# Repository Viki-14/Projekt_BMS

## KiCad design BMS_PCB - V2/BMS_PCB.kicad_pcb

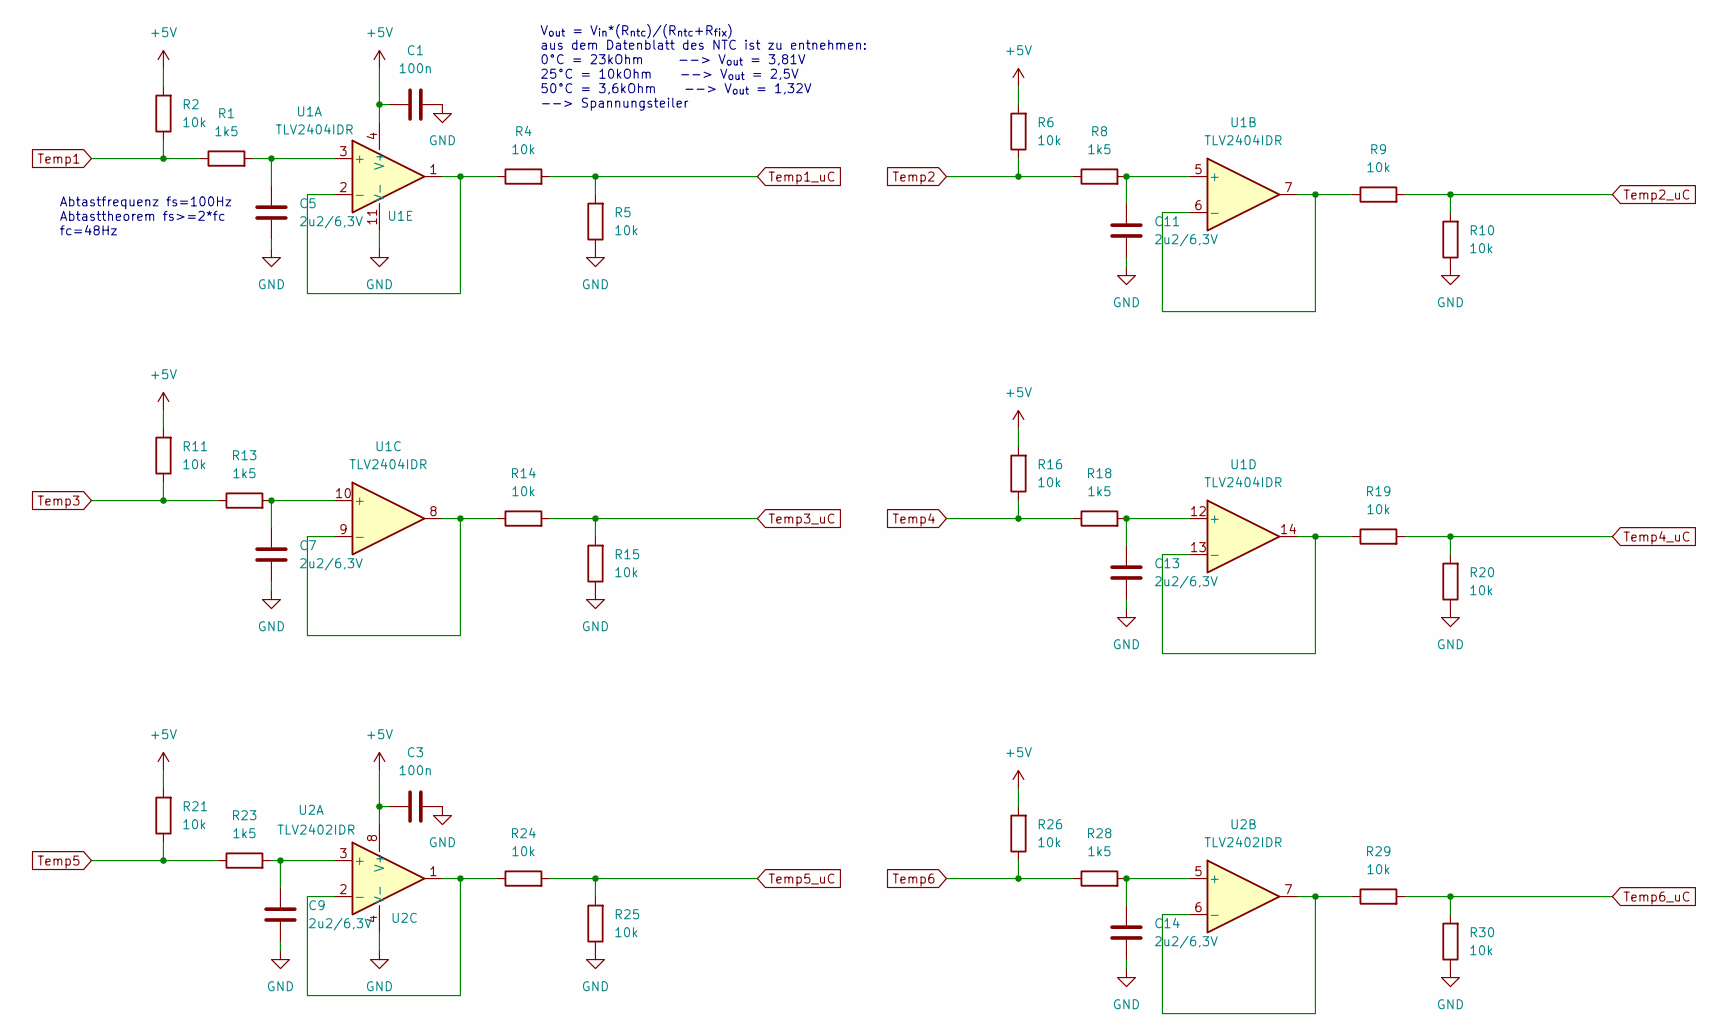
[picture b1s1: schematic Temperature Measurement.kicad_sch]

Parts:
C1, C3: 100n; C_0603_1608Metric_Pad1.08x0.95mm_HandSolder
C5, C7, C9, C11, C13, C14: 2u2/6,3V; C_0603_1608Metric_Pad1.08x0.95mm_HandSolder
R1, R8, R13, R18, R23, R28: 1k5; R_0603_1608Metric_Pad0.98x0.95mm_HandSolder
R2, R4, R5, R6, R9, R10, R11, R14, R15, R16, R19, R20, R21, R24, R25, R26, R29, R30: 10k; R_0603_1608Metric_Pad0.98x0.95mm_HandSolder
U1: TLV2404IDR; SOIC-14_3.9x8.7mm_P1.27mm
U2: TLV2402IDR; SOIC-8_3.9x4.9mm_P1.27mm

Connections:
+5V: C1.1, C3.1, R2.2, R6.2, R11.2, R16.2, R21.2, R26.2, U1.4 (V+), U2.8 (V+); also elsewhere on the board
GND: C1.2, C3.2, C5.2, C7.2, C9.2, C11.2, C13.2, C14.2, R5.1, R10.1, R15.1, R20.1, R25.1, R30.1, U1.11 (V-), U2.4 (V-); also elsewhere on the board
unnamed: C5.1, R1.2, U1.3 (+)
unnamed: R4.1, U1.1, U1.2 (-)
unnamed: C11.1, R8.2, U1.5 (+)
unnamed: R9.1, U1.6 (-), U1.7
unnamed: C7.1, R13.2, U1.10 (+)
unnamed: R14.1, U1.8, U1.9 (-)
unnamed: C13.1, R18.2, U1.12 (+)
unnamed: R19.1, U1.13 (-), U1.14
unnamed: C9.1, R23.2, U2.3 (+)
unnamed: R24.1, U2.1, U2.2 (-)
unnamed: C14.1, R28.2, U2.5 (+)
unnamed: R29.1, U2.6 (-), U2.7
Temp1: R1.1, R2.1; also elsewhere on the board
Temp1_uC: R4.2, R5.2; also elsewhere on the board
Temp2: R6.1, R8.1; also elsewhere on the board
Temp2_uC: R9.2, R10.2; also elsewhere on the board
Temp3: R11.1, R13.1; also elsewhere on the board
Temp3_uC: R14.2, R15.2; also elsewhere on the board
Temp4: R16.1, R18.1; also elsewhere on the board
Temp4_uC: R19.2, R20.2; also elsewhere on the board
Temp5: R21.1, R23.1; also elsewhere on the board
Temp5_uC: R24.2, R25.2; also elsewhere on the board
Temp6: R26.1, R28.1; also elsewhere on the board
Temp6_uC: R29.2, R30.2; also elsewhere on the board

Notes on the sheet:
V_{out} = V_{in}*(R_{ntc})/(R_{ntc}+R_{fix}) aus dem Datenblatt des NTC ist zu entnehmen: 0°C = 23kOhm --> V_{out} = 3,81V 25°C = 10kOhm --> V_{out} = 2,5V 50°C = 3,6kOhm --> V_{out} = 1,32V --> Spannungsteiler
Abtastfrequenz fs=100Hz Abtasttheorem fs>=2*fc fc=48Hz

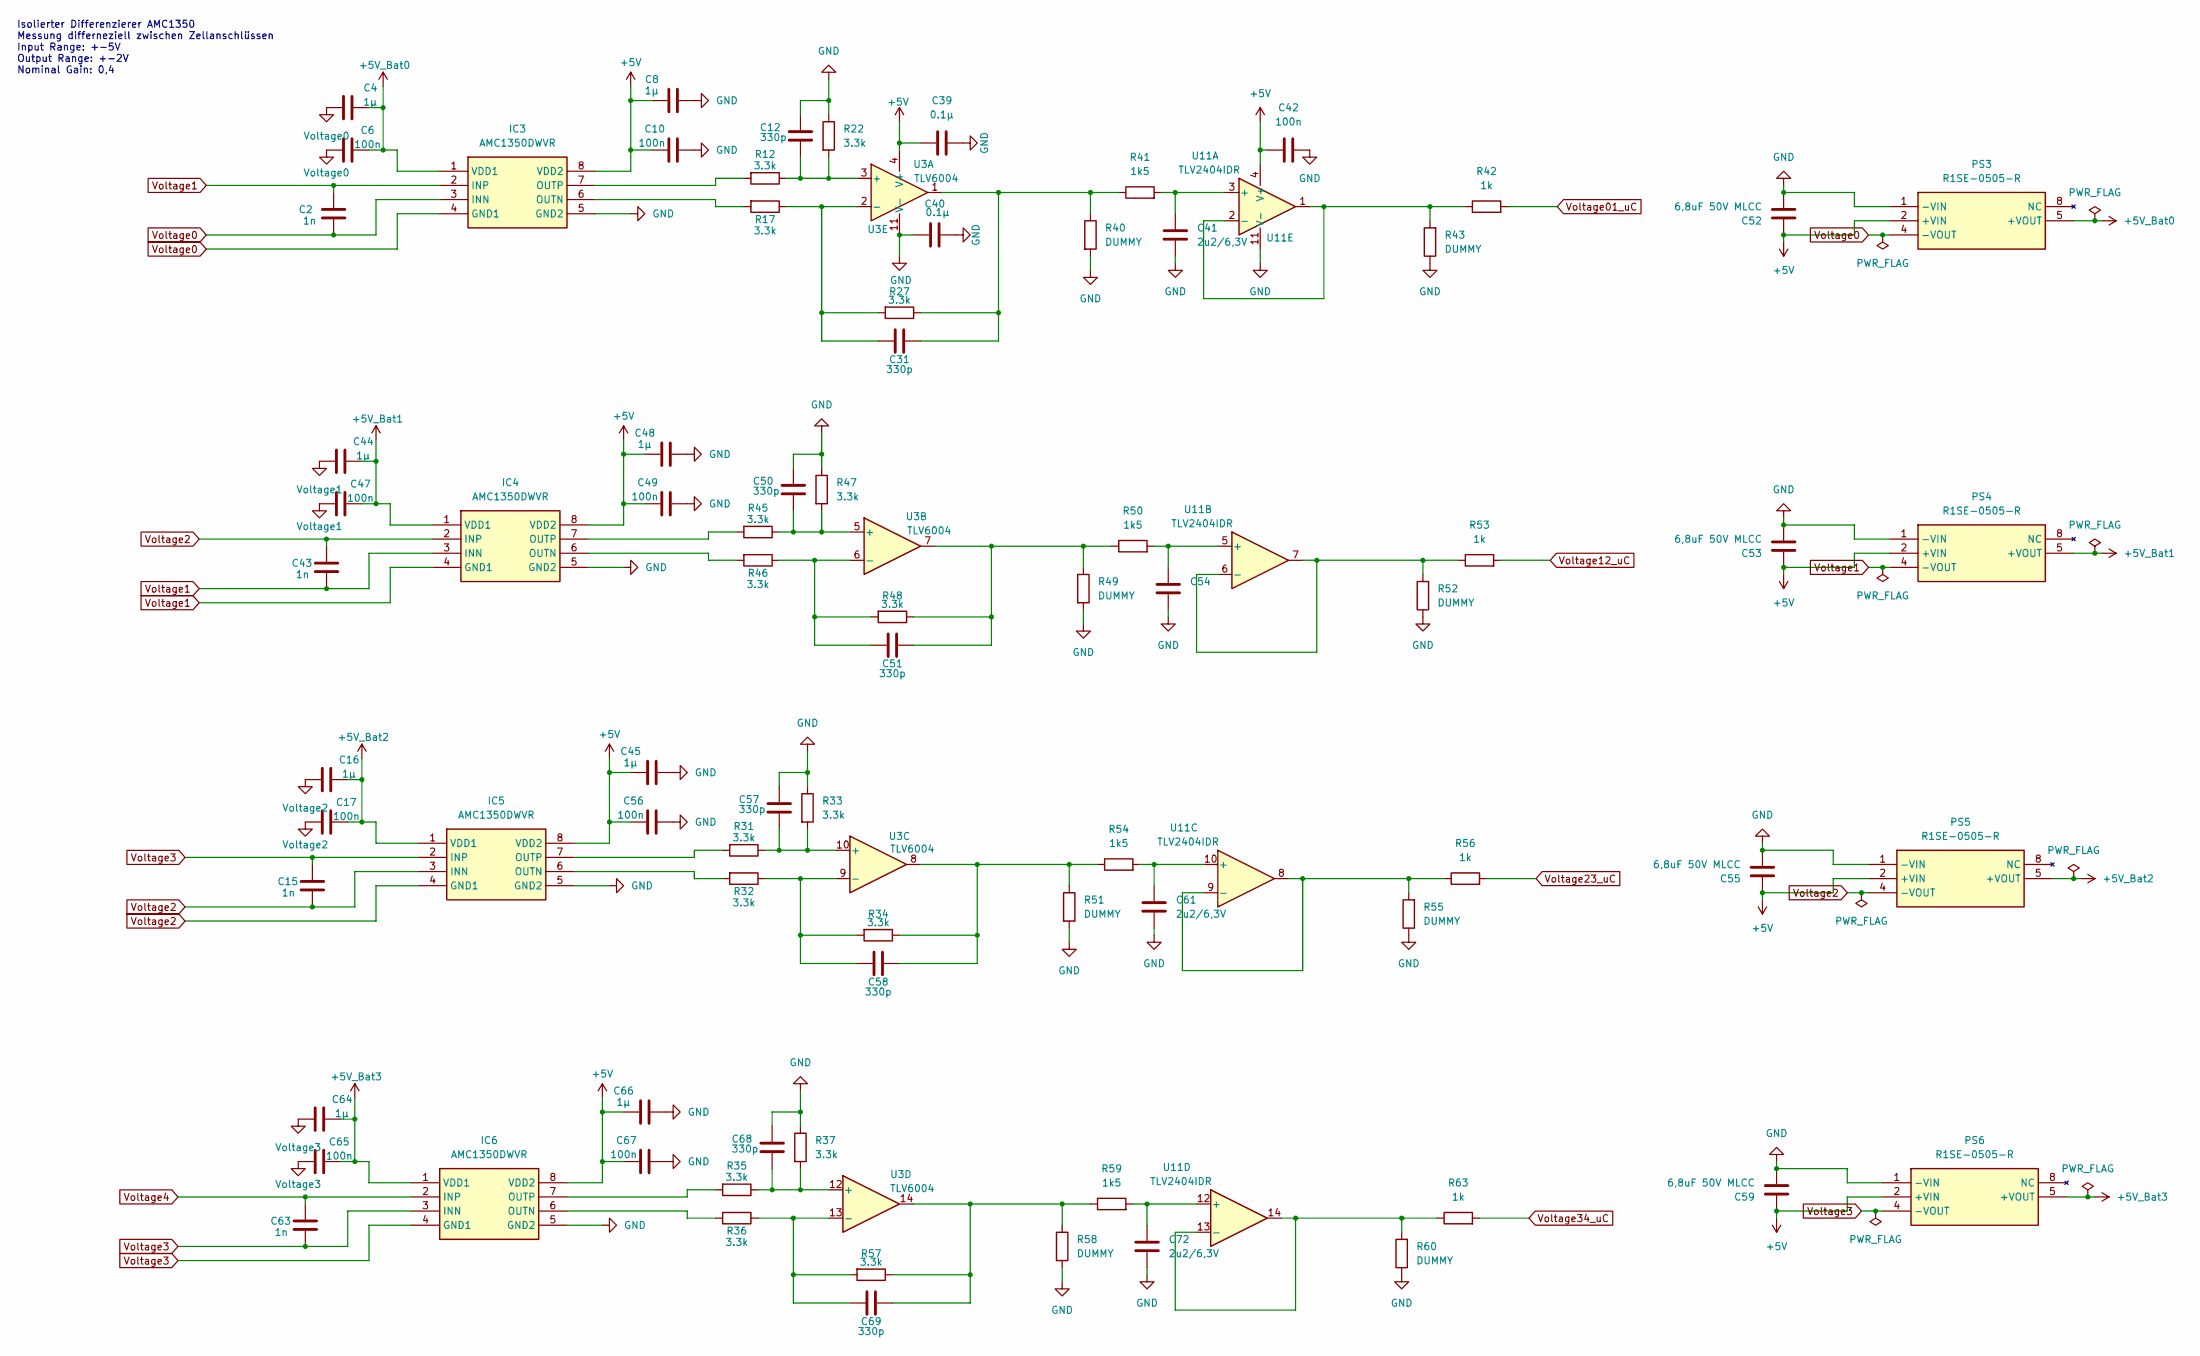
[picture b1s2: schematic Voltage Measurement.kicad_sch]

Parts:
C2, C15, C43, C63: 1n; C_0603_1608Metric_Pad1.08x0.95mm_HandSolder
C4, C8, C16, C44, C45, C48, C64, C66: 1µ; C_0603_1608Metric_Pad1.08x0.95mm_HandSolder
C6, C10, C17, C42, C47, C49, C56, C65, C67: 100n; C_0603_1608Metric_Pad1.08x0.95mm_HandSolder
C12, C31, C50, C51, C57, C58, C68, C69: 330p; C_0603_1608Metric_Pad1.08x0.95mm_HandSolder
C39, C40: 0.1µ; C_0603_1608Metric_Pad1.08x0.95mm_HandSolder
C41, C54, C61, C72: 2u2/6,3V; C_0603_1608Metric_Pad1.08x0.95mm_HandSolder
C52, C53, C55, C59: 6,8uF 50V MLCC; C_1206_3216Metric_Pad1.33x1.80mm_HandSolder
IC3, IC4, IC5, IC6: AMC1350DWVR; SOIC127P1150X280-8N; Mouser Part Number 595-AMC1350DWVR
PS3, PS4, PS5, PS6: R1SE-0505-R; R1SE0505; Mouser Part Number 919-R1SE-0505-R
R12, R17, R22, R27, R31, R32, R33, R34, R35, R36, R37, R45, R46, R47, R48, R57: 3.3k; R_0603_1608Metric_Pad0.98x0.95mm_HandSolder
R40, R43, R49, R51, R52, R55, R58, R60: DUMMY; R_0603_1608Metric_Pad0.98x0.95mm_HandSolder
R41, R50, R54, R59: 1k5; R_0603_1608Metric_Pad0.98x0.95mm_HandSolder
R42, R53, R56, R63: 1k; R_0603_1608Metric_Pad0.98x0.95mm_HandSolder
U3: TLV6004; TSSOP-14_4.4x5mm_P0.65mm
U11: TLV2404IDR; SOIC-14_3.9x8.7mm_P1.27mm

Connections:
+5V: C8.2, C10.1, C39.1, C42.1, C45.2, C48.2, C49.1, C52.1, C53.1, C55.1, C56.1, C59.1, C66.2, C67.1, IC3.8 (VDD2), IC4.8 (VDD2), IC5.8 (VDD2), IC6.8 (VDD2), PS3.2 (+VIN), PS4.2 (+VIN), PS5.2 (+VIN), PS6.2 (+VIN), U3.4 (V+), U11.4 (V+); also elsewhere on the board
+5V_Bat0: C4.1, C6.2, IC3.1 (VDD1), PS3.5 (+VOUT)
+5V_Bat1: C44.1, C47.2, IC4.1 (VDD1), PS4.5 (+VOUT)
+5V_Bat2: C16.1, C17.2, IC5.1 (VDD1), PS5.5 (+VOUT)
+5V_Bat3: C64.1, C65.2, IC6.1 (VDD1), PS6.5 (+VOUT)
GND: C8.1, C10.2, C12.1, C39.2, C40.1, C40.2, C41.2, C42.2, C45.1, C48.1, C49.2, C50.1, C52.2, C53.2, C54.2, C55.2, C56.2, C57.1, C59.2, C61.2, C66.1, C67.2, C68.1, C72.2, IC3.5 (GND2), IC4.5 (GND2), IC5.5 (GND2), IC6.5 (GND2), PS3.1 (-VIN), PS4.1 (-VIN), PS5.1 (-VIN), PS6.1 (-VIN), R22.1, R33.1, R37.1, R40.2, R43.1, R47.1, R49.2, R51.2, R52.1, R55.1, R58.2, R60.1, U3.11 (V-), U11.11 (V-); also elsewhere on the board
unnamed: C31.2, R27.1, R40.1, R41.1, U3.1
unnamed: C51.2, R48.1, R49.1, R50.1, U3.7
unnamed: C58.2, R34.1, R51.1, R54.1, U3.8
unnamed: C69.2, R57.1, R58.1, R59.1, U3.14
unnamed: IC3.6 (OUTN), R17.2
unnamed: IC3.7 (OUTP), R12.2
unnamed: IC4.6 (OUTN), R46.2
unnamed: IC4.7 (OUTP), R45.2
unnamed: IC5.6 (OUTN), R32.2
unnamed: IC5.7 (OUTP), R31.2
unnamed: IC6.6 (OUTN), R36.2
unnamed: IC6.7 (OUTP), R35.2
unnamed: C12.2, R12.1, R22.2, U3.3 (+)
unnamed: C31.1, R17.1, R27.2, U3.2 (-)
unnamed: C50.2, R45.1, R47.2, U3.5 (+)
unnamed: C51.1, R46.1, R48.2, U3.6 (-)
unnamed: C57.2, R31.1, R33.2, U3.10 (+)
unnamed: C58.1, R32.1, R34.2, U3.9 (-)
unnamed: C68.2, R35.1, R37.2, U3.12 (+)
unnamed: C69.1, R36.1, R57.2, U3.13 (-)
unnamed: C41.1, R41.2, U11.3 (+)
unnamed: R42.1, R43.2, U11.1, U11.2 (-)
unnamed: C54.1, R50.2, U11.5 (+)
unnamed: R52.2, R53.1, U11.6 (-), U11.7
unnamed: C61.1, R54.2, U11.10 (+)
unnamed: R55.2, R56.1, U11.8, U11.9 (-)
unnamed: C72.1, R59.2, U11.12 (+)
unnamed: R60.2, R63.1, U11.13 (-), U11.14
Voltage0: C2.2, C4.2, C6.1, IC3.3 (INN), IC3.4 (GND1), PS3.4 (-VOUT); also elsewhere on the board
Voltage1: C2.1, C43.2, C44.2, C47.1, IC3.2 (INP), IC4.3 (INN), IC4.4 (GND1), PS4.4 (-VOUT); also elsewhere on the board
Voltage01_uC: R42.2; also elsewhere on the board
Voltage2: C15.2, C16.2, C17.1, C43.1, IC4.2 (INP), IC5.3 (INN), IC5.4 (GND1), PS5.4 (-VOUT); also elsewhere on the board
Voltage3: C15.1, C63.2, C64.2, C65.1, IC5.2 (INP), IC6.3 (INN), IC6.4 (GND1), PS6.4 (-VOUT); also elsewhere on the board
Voltage4: C63.1, IC6.2 (INP); also elsewhere on the board
Voltage12_uC: R53.2; also elsewhere on the board
Voltage23_uC: R56.2; also elsewhere on the board
Voltage34_uC: R63.2; also elsewhere on the board

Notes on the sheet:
Isolierter Differenzierer AMC1350 Messung differneziell zwischen Zellanschlüssen Input Range: +-5V Output Range: +-2V Nominal Gain: 0,4

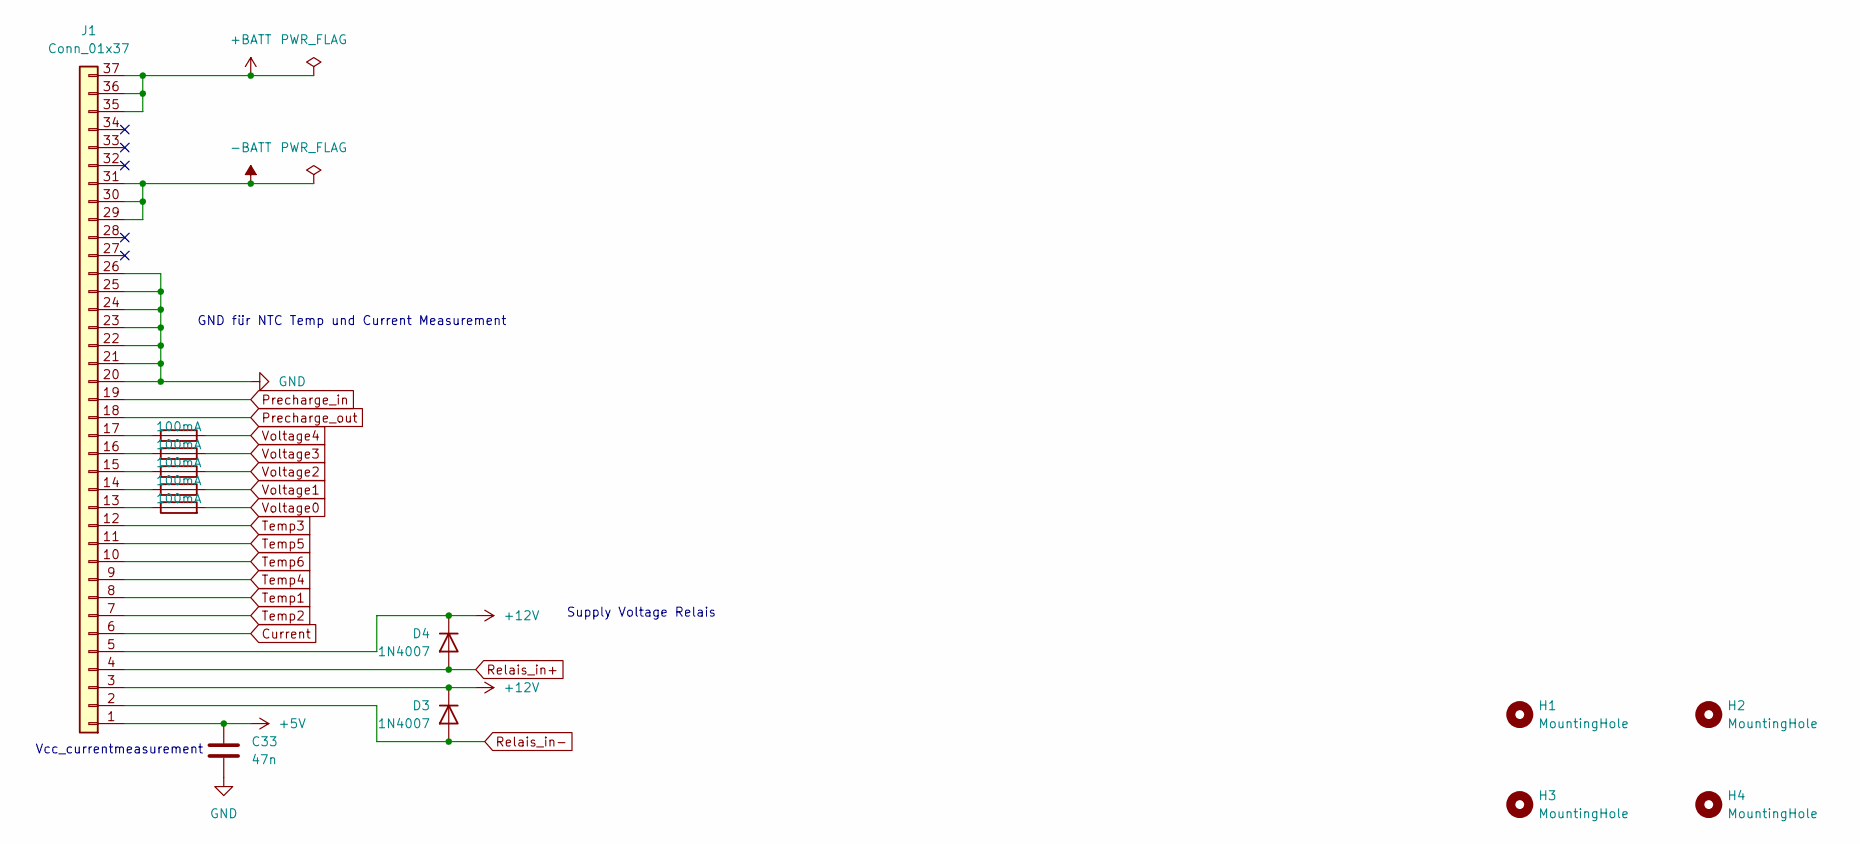
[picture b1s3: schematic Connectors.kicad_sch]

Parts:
C33: 47n; C_0603_1608Metric_Pad1.08x0.95mm_HandSolder
D3, D4: 1N4007; D_SMA
F1, F2, F3, F4, F6: 100mA; Fuse_Littelfuse-NANO2-451_453
H1, H2, H3, H4: MountingHole; MountingHole_3.5mm
J1: Conn_01x37; DSUB-37_Socket_Horizontal_P2.77x2.84mm_EdgePinOffset14.56mm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

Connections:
+12V: D3.1 (K), D4.1 (K), J1.3, J1.5; also elsewhere on the board
+BATT: J1.35, J1.36, J1.37; also elsewhere on the board
-BATT: J1.29, J1.30, J1.31; also elsewhere on the board
Current: J1.6; also elsewhere on the board
GND: C33.2, J1.20, J1.21, J1.22, J1.23, J1.24, J1.25, J1.26; also elsewhere on the board
unnamed: F6.1, J1.13
unnamed: F4.1, J1.14
unnamed: F3.1, J1.15
unnamed: F2.1, J1.16
unnamed: F1.1, J1.17
Precharge_in: J1.19; also elsewhere on the board
Precharge_out: J1.18; also elsewhere on the board
Relais_in+: D4.2 (A), J1.4; also elsewhere on the board
Relais_in-: D3.2 (A), J1.2; also elsewhere on the board
Temp1: J1.8; also elsewhere on the board
Temp2: J1.7; also elsewhere on the board
Temp3: J1.12; also elsewhere on the board
Temp4: J1.9; also elsewhere on the board
Temp5: J1.11; also elsewhere on the board
Temp6: J1.10; also elsewhere on the board
Voltage0: F6.2; also elsewhere on the board
Voltage1: F4.2; also elsewhere on the board
Voltage2: F3.2; also elsewhere on the board
Voltage3: F2.2; also elsewhere on the board
Voltage4: F1.2; also elsewhere on the board

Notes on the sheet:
Supply Voltage Relais
Vcc_currentmeasurement
GND für NTC Temp und Current Measurement

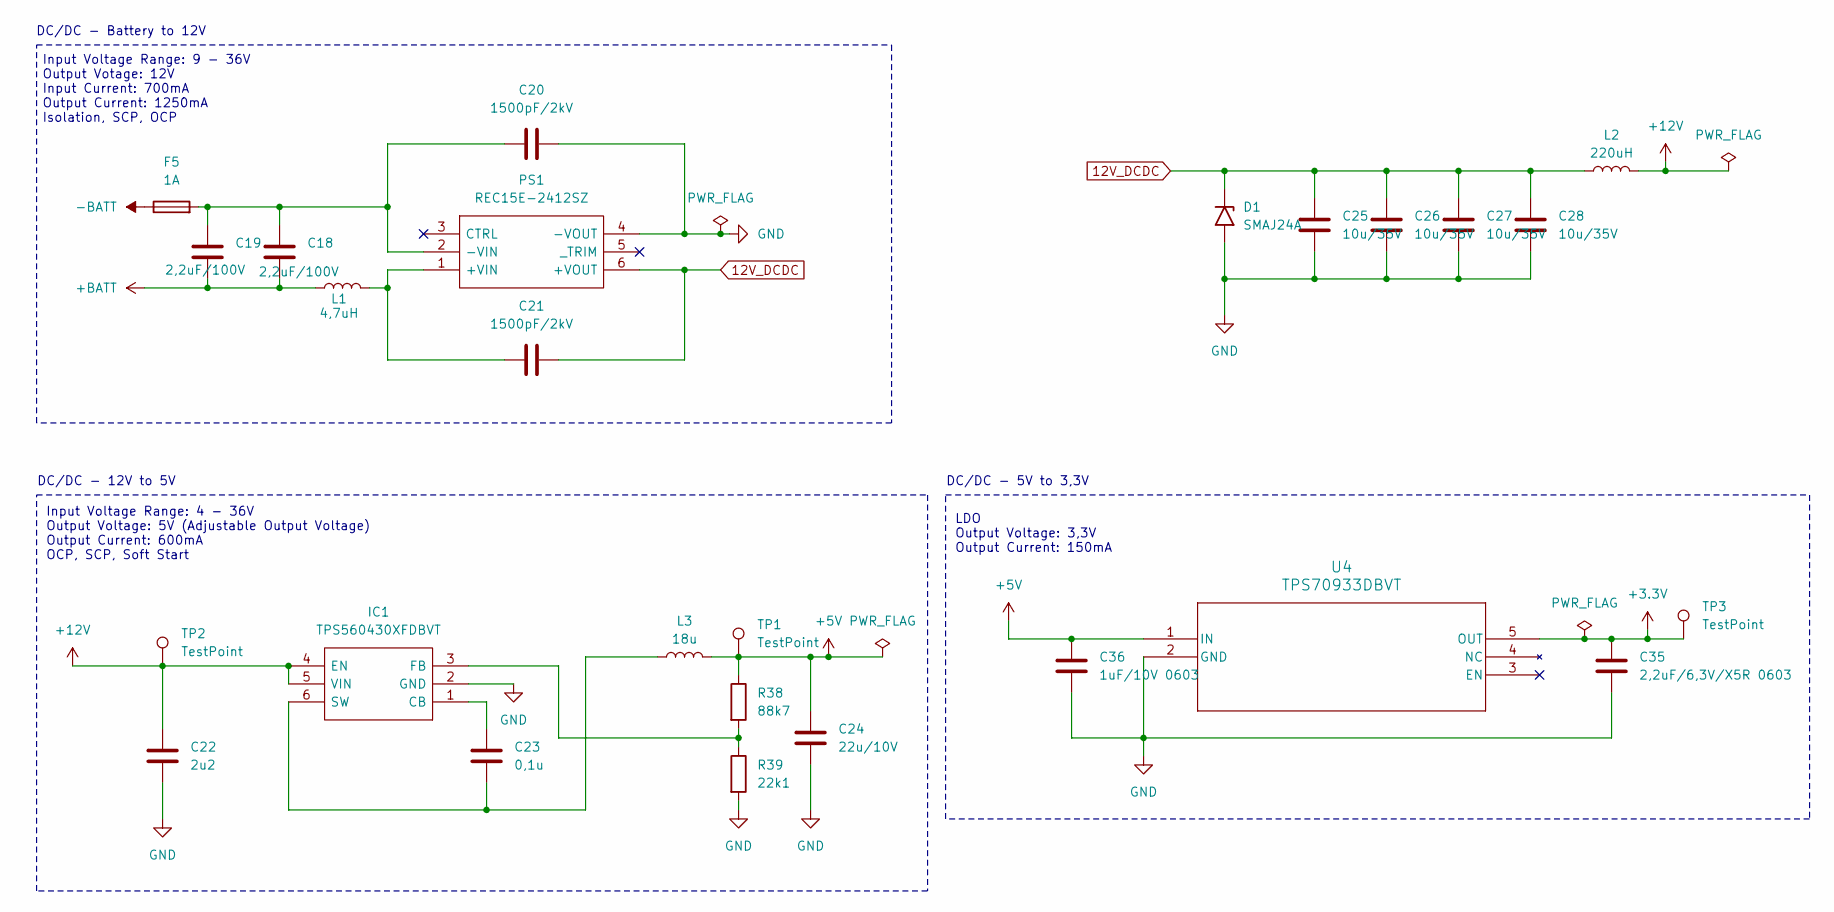
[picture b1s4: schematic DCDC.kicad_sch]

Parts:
C18, C19: 2,2uF/100V; C_0805_2012Metric_Pad1.18x1.45mm_HandSolder
C20, C21: 1500pF/2kV; C_1206_3216Metric_Pad1.33x1.80mm_HandSolder
C22: 2u2; C_0603_1608Metric_Pad1.08x0.95mm_HandSolder
C23: 0,1u; C_0603_1608Metric_Pad1.08x0.95mm_HandSolder
C24: 22u/10V; C_0603_1608Metric_Pad1.08x0.95mm_HandSolder
C25, C26, C27, C28: 10u/35V; C_0603_1608Metric_Pad1.08x0.95mm_HandSolder
C35: 2,2uF/6,3V/X5R 0603; C_0603_1608Metric_Pad1.08x0.95mm_HandSolder
C36: 1uF/10V 0603; C_0603_1608Metric_Pad1.08x0.95mm_HandSolder
D1: SMAJ24A; D_SMA
F5: 1A; Fuseholder_Littelfuse_Nano2_154x
IC1: TPS560430XFDBVT; SOT-23-6_Handsoldering; Mouser Part Number 595-TPS560430XFDBVT
L1: 4,7uH; L_Coilcraft_XxL4020
L2: 220uH; L_Wuerth_WE-PD2-Typ-L
L3: 18u; L_Bourns_SDR0604
PS1: REC15E-2412SZ; CONV_REC15E-2412SZ; Mouser Part Number 919-REC15E-2412SZ
R38: 88k7; R_0603_1608Metric_Pad0.98x0.95mm_HandSolder
R39: 22k1; R_0603_1608Metric_Pad0.98x0.95mm_HandSolder
TP1, TP2, TP3: TestPoint; TestPoint_Pad_D1.0mm
U4: TPS70933DBVT; SOT-23-5_HandSoldering

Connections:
12V_DCDC: C21.2, C25.1, C26.1, C27.1, C28.1, D1.1 (A1), L2.1, PS1.6 (+VOUT)
+5V: C24.1, C36.1, L3.2, R38.1, TP1.1, U4.1 (IN); also elsewhere on the board
+12V: C22.1, IC1.4 (EN), IC1.5 (VIN), L2.2, TP2.1; also elsewhere on the board
+BATT: C18.2, C19.2, L1.1; also elsewhere on the board
-BATT: F5.1; also elsewhere on the board
GND: C20.2, C22.2, C24.2, C25.2, C26.2, C27.2, C28.2, C35.2, C36.2, D1.2 (A2), IC1.2 (GND), PS1.4 (-VOUT), R39.2, U4.2 (GND); also elsewhere on the board
unnamed: C23.1, IC1.1 (CB)
unnamed: IC1.3 (FB), R38.2, R39.1
unnamed: C23.2, IC1.6 (SW), L3.1
unnamed: C21.1, L1.2, PS1.1 (+VIN)
unnamed: C18.1, C19.1, C20.1, F5.2, PS1.2 (-VIN)

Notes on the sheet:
Input Voltage Range: 4 - 36V Output Voltage: 5V (Adjustable Output Voltage) Output Current: 600mA OCP, SCP, Soft Start
DC/DC - Battery to 12V
DC/DC - 12V to 5V
LDO Output Voltage: 3,3V Output Current: 150mA
Input Voltage Range: 9 - 36V Output Votage: 12V Input Current: 700mA Output Current: 1250mA Isolation, SCP, OCP
DC/DC - 5V to 3,3V

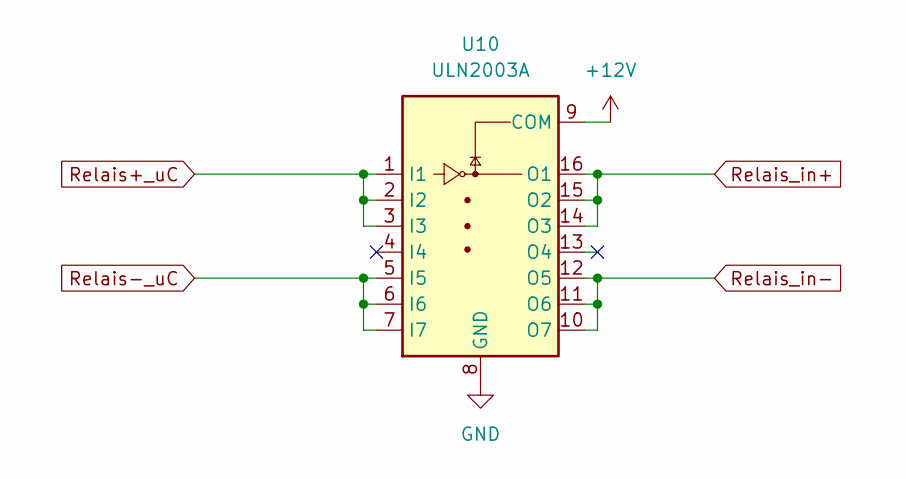
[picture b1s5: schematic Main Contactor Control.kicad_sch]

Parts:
U10: ULN2003A; SOIC-16_3.9x9.9mm_P1.27mm

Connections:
+12V: U10.9 (COM); also elsewhere on the board
GND: U10.8 (GND); also elsewhere on the board
Relais+_uC: U10.1 (I1), U10.2 (I2), U10.3 (I3); also elsewhere on the board
Relais-_uC: U10.5 (I5), U10.6 (I6), U10.7 (I7); also elsewhere on the board
Relais_in+: U10.14 (O3), U10.15 (O2), U10.16 (O1); also elsewhere on the board
Relais_in-: U10.10 (O7), U10.11 (O6), U10.12 (O5); also elsewhere on the board

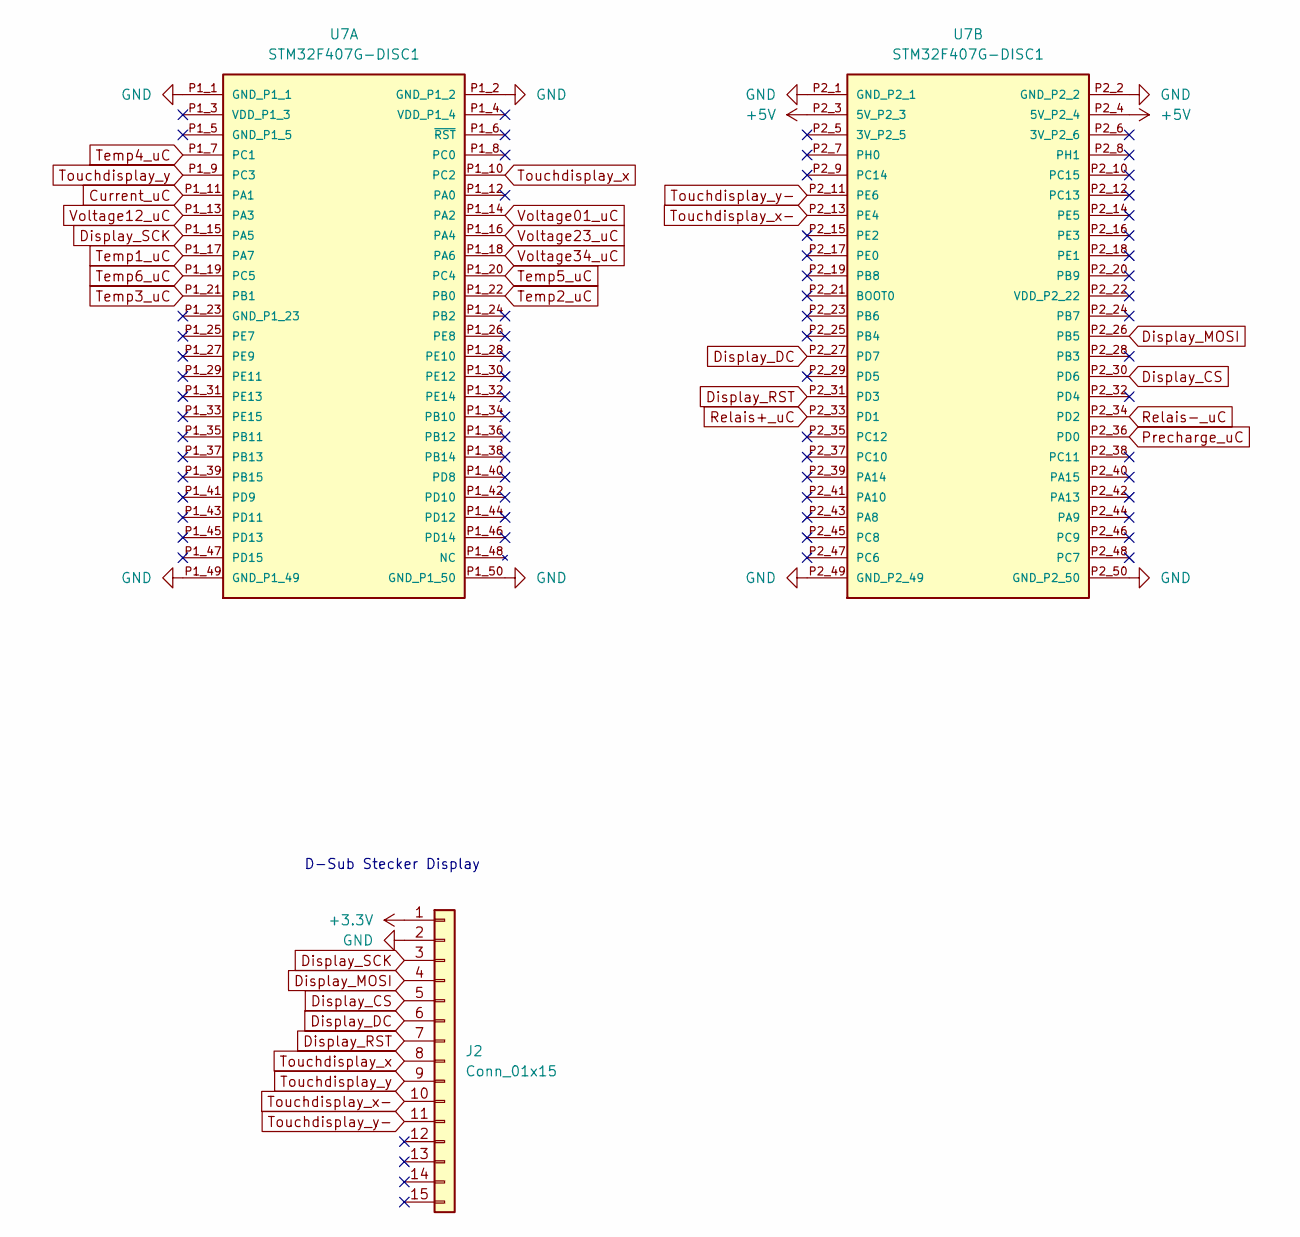
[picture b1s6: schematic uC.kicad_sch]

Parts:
J2: Conn_01x15; DSUB-15_Socket_Horizontal_P2.77x2.84mm_EdgePinOffset14.56mm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
U7: STM32F407G-DISC1; MODULE_STM32F407G-DISC1; PARTREV 7

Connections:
+5V: U7.P2_3 (5V_P2_3), U7.P2_4 (5V_P2_4); also elsewhere on the board
Current_uC: U7.P1_11 (PA1); also elsewhere on the board
Display_CS: J2.5, U7.P2_30 (PD6)
Display_DC: J2.6, U7.P2_27 (PD7)
Display_MOSI: J2.4, U7.P2_26 (PB5)
Display_RST: J2.7, U7.P2_31 (PD3)
Display_SCK: J2.3, U7.P1_15 (PA5)
GND: J2.2, U7.P1_1 (GND_P1_1), U7.P1_2 (GND_P1_2), U7.P1_49 (GND_P1_49), U7.P1_50 (GND_P1_50), U7.P2_1 (GND_P2_1), U7.P2_2 (GND_P2_2), U7.P2_49 (GND_P2_49), U7.P2_50 (GND_P2_50); also elsewhere on the board
Precharge_uC: U7.P2_36 (PD0); also elsewhere on the board
Relais+_uC: U7.P2_33 (PD1); also elsewhere on the board
Relais-_uC: U7.P2_34 (PD2); also elsewhere on the board
Temp1_uC: U7.P1_17 (PA7); also elsewhere on the board
Temp2_uC: U7.P1_22 (PB0); also elsewhere on the board
Temp3_uC: U7.P1_21 (PB1); also elsewhere on the board
Temp4_uC: U7.P1_7 (PC1); also elsewhere on the board
Temp5_uC: U7.P1_20 (PC4); also elsewhere on the board
Temp6_uC: U7.P1_19 (PC5); also elsewhere on the board
Touchdisplay_x: J2.8, U7.P1_10 (PC2)
Touchdisplay_x-: J2.10, U7.P2_13 (PE4)
Touchdisplay_y: J2.9, U7.P1_9 (PC3)
Touchdisplay_y-: J2.11, U7.P2_11 (PE6)
Voltage01_uC: U7.P1_14 (PA2); also elsewhere on the board
Voltage12_uC: U7.P1_13 (PA3); also elsewhere on the board
Voltage23_uC: U7.P1_16 (PA4); also elsewhere on the board
Voltage34_uC: U7.P1_18 (PA6); also elsewhere on the board

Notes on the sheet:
D-Sub Stecker Display

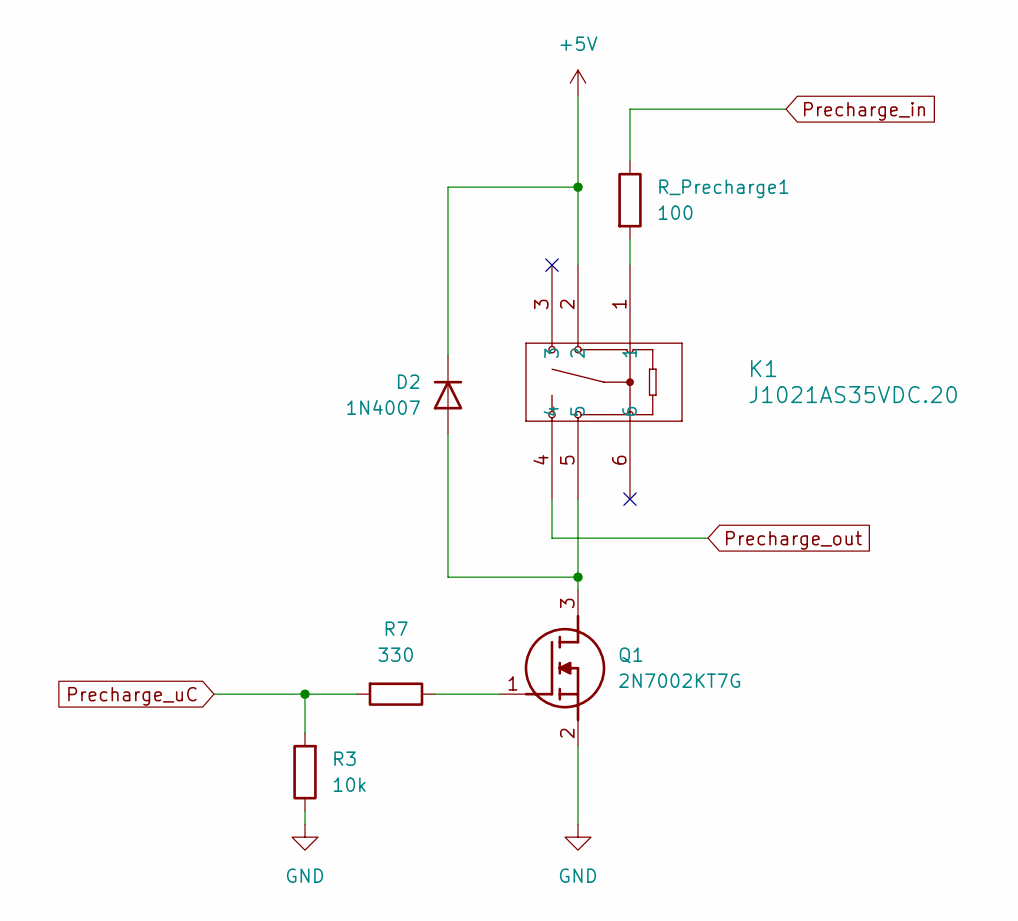
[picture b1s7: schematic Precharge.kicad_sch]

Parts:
D2: 1N4007; D_SMA
K1: J1021AS35VDC.20; J1021AS_CRS
Q1: 2N7002KT7G; SOT-23-3; Mouser Part Number 863-2N7002KT7G
R3: 10k; R_0603_1608Metric_Pad0.98x0.95mm_HandSolder
R7: 330; R_0603_1608Metric_Pad0.98x0.95mm_HandSolder
R_Precharge1: 100; R_2816_7142Metric_Pad3.20x4.45mm_HandSolder

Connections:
+5V: D2.1 (K), K1.2; also elsewhere on the board
GND: Q1.2 (S), R3.1; also elsewhere on the board
unnamed: D2.2 (A), K1.5, Q1.3 (D)
unnamed: Q1.1 (G), R7.1
Precharge_in: R_Precharge1.1; also elsewhere on the board
Precharge_out: K1.4; also elsewhere on the board
Precharge_uC: R3.2, R7.2; also elsewhere on the board

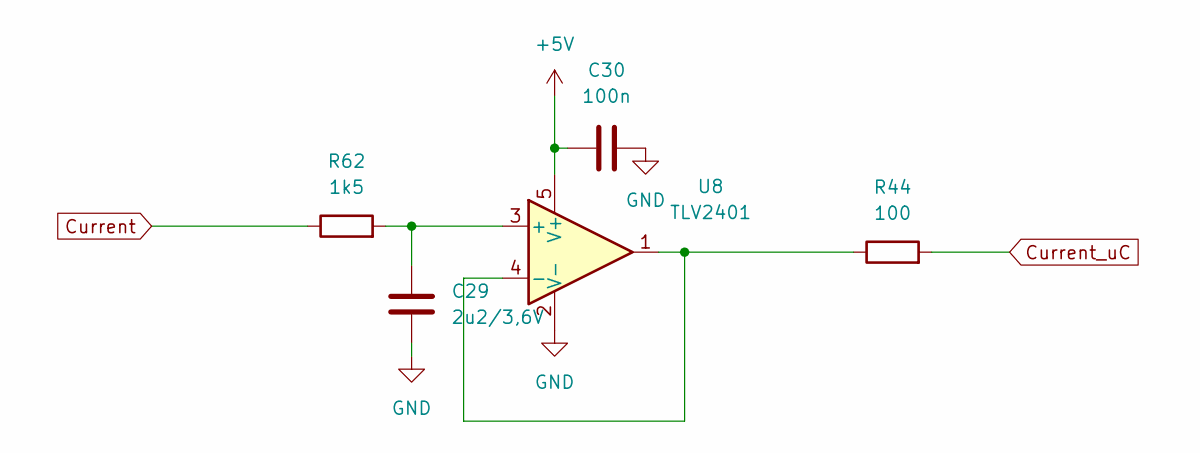
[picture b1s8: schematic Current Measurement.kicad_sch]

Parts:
C29: 2u2/3,6V; C_0603_1608Metric_Pad1.08x0.95mm_HandSolder
C30: 100n; C_0603_1608Metric_Pad1.08x0.95mm_HandSolder
R44: 100; R_0603_1608Metric_Pad0.98x0.95mm_HandSolder
R62: 1k5; R_0603_1608Metric_Pad0.98x0.95mm_HandSolder
U8: TLV2401; SOT-23-5_HandSoldering

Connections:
+5V: C30.1, U8.5 (V+); also elsewhere on the board
Current: R62.1; also elsewhere on the board
Current_uC: R44.2; also elsewhere on the board
GND: C29.2, C30.2, U8.2 (V-); also elsewhere on the board
unnamed: C29.1, R62.2, U8.3 (+)

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
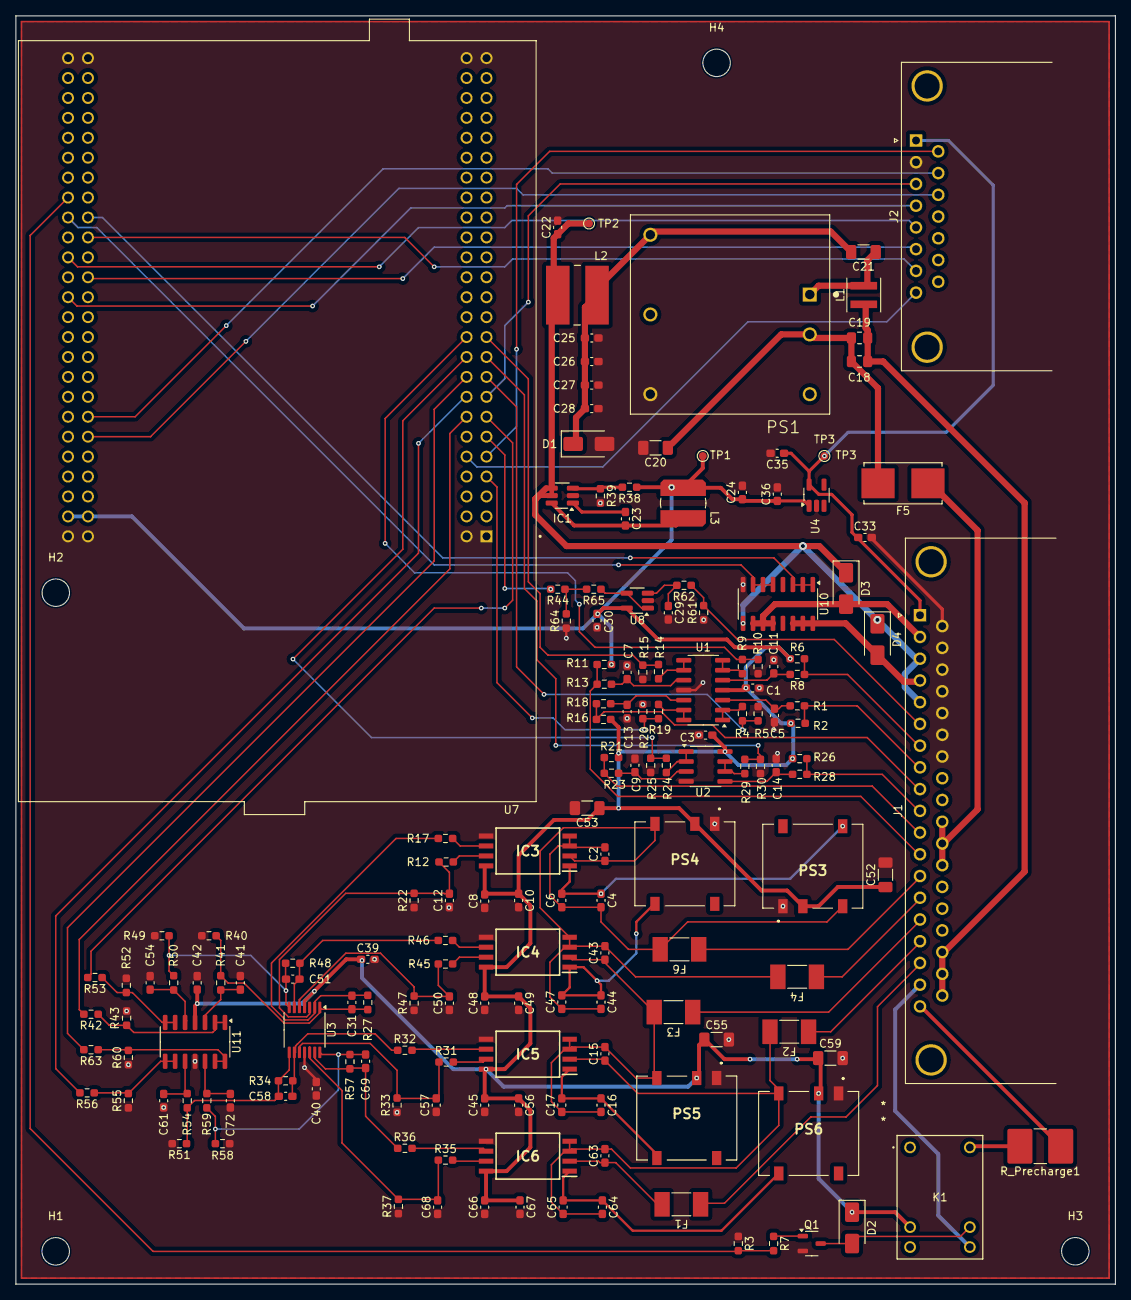
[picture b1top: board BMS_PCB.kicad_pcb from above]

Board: 2 copper layers, 140.2 x 161.7 mm, 171 parts (0 on the bottom side), 106 nets.

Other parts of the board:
R61, R64, R65: DUMMY; R_0603_1608Metric_Pad0.98x0.95mm_HandSolder

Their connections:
Current: R61.2; also elsewhere on the board
GND: R61.1, R64.1; also elsewhere on the board

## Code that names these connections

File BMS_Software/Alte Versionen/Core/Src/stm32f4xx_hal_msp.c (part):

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    __HAL_RCC_GPIOA_CLK_ENABLE();
    __HAL_RCC_GPIOB_CLK_ENABLE();
    /**ADC1 GPIO Configuration
    PC1     ------> ADC1_IN11
    PA7     ------> ADC1_IN7
    PC4     ------> ADC1_IN14
    PC5     ------> ADC1_IN15
    PB0     ------> ADC1_IN8
    PB1     ------> ADC1_IN9
    */
    GPIO_InitStruct.Pin = Temp_4_Pin|Temp_5_Pin|Temp_6_Pin;
    GPIO_InitStruct.Mode = GPIO_MODE_ANALOG;
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
    __HAL_RCC_GPIOA_CLK_ENABLE();
    /**ADC2 GPIO Configuration
    PA2     ------> ADC2_IN2
    PA3     ------> ADC2_IN3
    PA4     ------> ADC2_IN4
    PA6     ------> ADC2_IN6
    */
    GPIO_InitStruct.Pin = Voltage01_Pin|Voltage12_Pin|Voltage23_Pin|Voltage34_Pin;
    GPIO_InitStruct.Mode = GPIO_MODE_ANALOG;
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    __HAL_RCC_GPIOC_CLK_ENABLE();
    __HAL_RCC_GPIOA_CLK_ENABLE();
    /**ADC3 GPIO Configuration
    PC2     ------> ADC3_IN12
    PC3     ------> ADC3_IN13
    PA1     ------> ADC3_IN1
    */
    GPIO_InitStruct.Pin = Touchdisplay_x_Pin|Touchdisplay_y_Pin;
    GPIO_InitStruct.Mode = GPIO_MODE_ANALOG;
    GPIO_InitStruct.Pull = GPIO_NOPULL;
    HAL_GPIO_Init(GPIOC, &GPIO_InitStruct);

    GPIO_InitStruct.Pin = Current_Pin;
    GPIO_InitStruct.Mode = GPIO_MODE_ANALOG;
    GPIO_InitStruct.Pull = GPIO_NOPULL;
    HAL_GPIO_Init(Current_GPIO_Port, &GPIO_InitStruct);

    /* ADC3 DMA Init */
    /* ADC3 Init */
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    __HAL_RCC_ADC1_CLK_DISABLE();

    /**ADC1 GPIO Configuration
    PC1     ------> ADC1_IN11
    PA7     ------> ADC1_IN7
    PC4     ------> ADC1_IN14
    PC5     ------> ADC1_IN15
    PB0     ------> ADC1_IN8
    PB1     ------> ADC1_IN9
    */
    HAL_GPIO_DeInit(GPIOC, Temp_4_Pin|Temp_5_Pin|Temp_6_Pin);

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    __HAL_RCC_ADC2_CLK_DISABLE();

    /**ADC2 GPIO Configuration
    PA2     ------> ADC2_IN2
    PA3     ------> ADC2_IN3
    PA4     ------> ADC2_IN4
    PA6     ------> ADC2_IN6
    */
    HAL_GPIO_DeInit(GPIOA, Voltage01_Pin|Voltage12_Pin|Voltage23_Pin|Voltage34_Pin);

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    __HAL_RCC_ADC3_CLK_DISABLE();

    /**ADC3 GPIO Configuration
    PC2     ------> ADC3_IN12
    PC3     ------> ADC3_IN13
    PA1     ------> ADC3_IN1
    */
    HAL_GPIO_DeInit(GPIOC, Touchdisplay_x_Pin|Touchdisplay_y_Pin);

    HAL_GPIO_DeInit(Current_GPIO_Port, Current_Pin);

    /* ADC3 DMA DeInit */
    HAL_DMA_DeInit(hadc->DMA_Handle);
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    __HAL_RCC_GPIOA_CLK_ENABLE();
    __HAL_RCC_GPIOB_CLK_ENABLE();
    /**SPI1 GPIO Configuration
    PA5     ------> SPI1_SCK
    PB4     ------> SPI1_MISO
    PB5     ------> SPI1_MOSI
    */
    GPIO_InitStruct.Pin = GPIO_PIN_5;
    GPIO_InitStruct.Mode = GPIO_MODE_AF_PP;
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    __HAL_RCC_SPI1_CLK_DISABLE();

    /**SPI1 GPIO Configuration
    PA5     ------> SPI1_SCK
    PB4     ------> SPI1_MISO
    PB5     ------> SPI1_MOSI
    */
    HAL_GPIO_DeInit(GPIOA, GPIO_PIN_5);

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
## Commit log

2025-04-24 Test
    Test
2025-04-24 test
2025-04-24 Update uC.kicad_sch
    changed gpio pins
2025-04-25 Freitag
    Ich habe heute viele Bauteile zusammengesetzt. Die Leiterbahnen würde ich eher zum Schluss machen.
2025-04-27 Sonntag
    Ich habe das Layout weitergemacht, die restlichen Schaltungen zusammengestellt und das meiste bereits verbunden. Problem sind noch die PS-Boxen (R1SE-0505-R), die für die Voltage Messung noch angesch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
2025-04-28 Montag, 28.04.
    Pin Belegung PCB geändert, noch nicht in Schematics
    PS-Boxen platziert
    80 % fertig verteilt und verbunden
2025-04-28 Changes Schematic
    - Symbol Relais
    - add DUMMY
    - changed Fuses 100mA
2025-04-29 Footprints changes
    -U10
    -uC pins/SPI changes
    - Fuses
    - DSUB
    - reupload layout
    - etc.
2025-04-29 Connector
    Ich hab die Pinbelegung vom DSUB Stecker in Schematics geändert
2025-04-29 Dienstag, 29.04.
    Layout soweit fertig gestellt, Probleme noch mit Footprints
2025-04-29 Footprints
2025-04-30 kleine Änderungen
    Grounding angepasst
    Connector angepasst
    Beschriftung angepasst
2025-04-30 Bugfixes
    noch ein paar Fehler ausgemerzt
2025-04-30 Mittwoch 30.04.
    Quadratisch Praktisch Gut
2025-05-02 Bohrungen platziert
2025-05-02 Bugfix
2025-05-02 Relais_in+ Leiterbahn vergrößert
2025-05-02 Bugfix Leiterbahn
2025-05-02 Edge Cut hinzugefügt
2025-05-03 changes schematic
    still missing: uC pins
2025-05-04 schematic uC
    changes schematic uC
2025-05-04 few changes
2025-05-04 Freilaufdiode
2025-05-04 pdf_v3
2025-05-04 Sonntag, 04.05.
    Leiterbahndicken angepasst, Bohrlöcher erneuert, µC final angeschlossen, letzte Bugfixes
2025-05-04 MountingHoles hinzugefügt
    MountingHoles sind jetzt auch in den Schematics
2025-05-04 Update
    Leiterbahndicke +5V von 0,4 auf 0,5 mm geändert
2025-05-04 Update 2
    eine Leiterbahn GND von 0,2 auf 0,3 mm verbreitert
2025-05-04 Bohrlöcher
    Löcher auf 3,5 mm geändert
2025-05-04 Bohrlöcher geändert
2025-05-04 12V auf 0,8 mm
2025-05-05 GND verbunden
2025-05-05 Bugfix
    Capacity und Resistors
2025-05-05 Update
    Bohrlöcher
2025-05-05 Update Step
2025-05-05 Gerber Files
2025-05-12 V1
    Erste Übergabe der Softwaredateien
2025-05-12 Mit Buttonvariable für Display
2025-05-17 BMS_Software_Project
    Softwareproject (Stand 12.05.25)
2025-05-18 Create Batterymanagementsystem_current.zip
    Erweiterung zu C++ Projekt
    Hinzufügen von Display files (noch fehlerhaft --> cmsis_os.h file nicht definiert (RTOS Notwendigkeit?))
2025-05-20 Display Erweiterung
    Erweiterung der Files und Start der Fehlerbehebung der Files
2025-05-21 Erweiterung Display Funktionalitäten
    Hinzufügen permanenter Display Schaltflächen
    Fortsetzung: Ausbesserungen Fehlermeldungen
2025-05-27 Initialisierung Display files
    Hinzufügen (hoffentlich aller) benötigter Files, die für das Display notwendig sind
2025-06-02 Erweiterungen Display-Funktionalitäten
    Nahezu Fertigstellung; Feinheiten / Kleinigkeiten noch ausstehend
2025-06-02 Umbenennung Ordner (Reihenfolge)
    Umbenennung, sodass die Versionen chronologisch angeordnet bleiben
2025-06-03 Hinzufügen globaler Variable buttonContactor für Relais/Schütz-Ansteuerung
2025-06-03 Zusammenführung der Software
2025-06-05 Zusammenführung (mit Fehler)
2025-06-13 Create Batteriemanagementsystem_13_06_ohne_Buffer_Display.zip
    nur ADC-Messung und state machine ohne Display + Buffer
2025-06-13 Display-Code-Änderungen
2025-06-17 Neuaufsetzung Projekt und Fehlersuche
2025-06-17 Hinzufügen der Clock-Config
2025-06-24 v1: Normale Version; v2: FreeRTOS Grundversion
2025-06-25 Finale Version (Kevin)
2025-06-28 schematic überarbeitet
2025-07-03 Ordner-Struktur geändert

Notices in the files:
BMS_Software/Alte Versionen/Core/Src/stm32f4xx_hal_msp.c:
Copyright (c) 2025 STMicroelectronics.
All rights reserved.
This software is licensed under terms that can be found in the LICENSE file
